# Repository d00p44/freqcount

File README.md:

# freqcount
accurate frequency counter

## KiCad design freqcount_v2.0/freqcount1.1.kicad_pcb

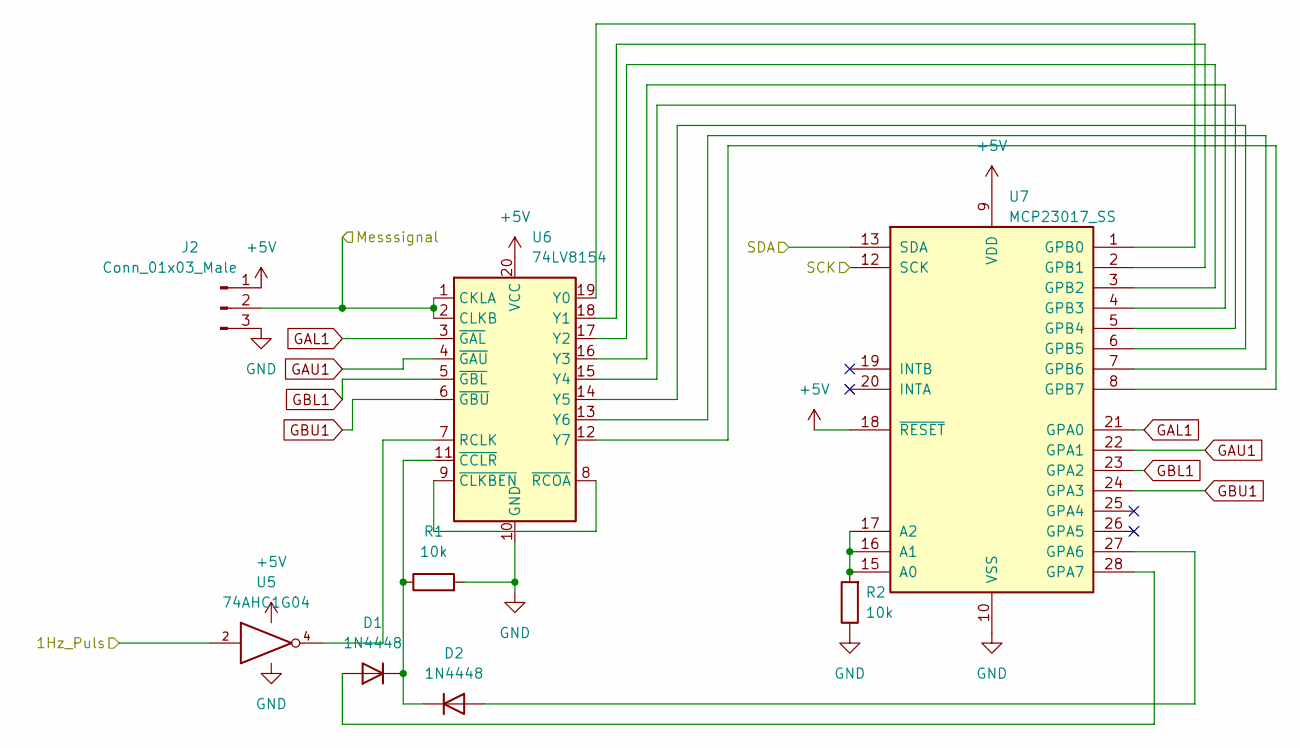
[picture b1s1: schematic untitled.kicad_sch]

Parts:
D1, D2: 1N4448; D_SOD-323
J2: Conn_01x03_Male; JST_PH_B3B-PH-K_1x03_P2.00mm_Vertical
R1, R2: 10k; R_0603_1608Metric
U5: 74AHC1G04; SOT-23-5
U6: 74LV8154; TSSOP-20_4.4x6.5mm_P0.65mm
U7: MCP23017_SS; SSOP-28_5.3x10.2mm_P0.65mm

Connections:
+5V: J2.1, U5.5 (VCC), U6.20 (VCC), U7.9 (VDD), U7.18 (~RESET); also elsewhere on the board
/ESP/SCK: U7.12 (SCK); also elsewhere on the board
/ESP/SDA: U7.13 (SDA); also elsewhere on the board
/Teiler_1Hz/1Hz_Puls: U5.2; also elsewhere on the board
/Zaehler_Messsignal/Messsignal: J2.2, U6.1 (CKLA), U6.2 (CLKB); also elsewhere on the board
GAL1: U6.3 (~GAL), U7.21 (GPA0)
GAU1: U6.4 (~GAU), U7.22 (GPA1)
GBL1: U6.5 (~GBL), U7.23 (GPA2)
GBU1: U6.6 (~GBU), U7.24 (GPA3)
GND: J2.3, R1.2, R2.1, U5.3 (GND), U6.10 (GND), U7.10 (VSS); also elsewhere on the board
unnamed: D1.1 (K), D2.1 (K), R1.1, U6.11 (~CCLR)
unnamed: D1.2 (A), U7.28 (GPA7)
unnamed: D2.2 (A), U7.27 (GPA6)
unnamed: R2.2, U7.15 (A0), U7.16 (A1), U7.17 (A2)
unnamed: U5.4, U6.7 (RCLK)
unnamed: U6.8 (~RCOA), U6.9 (~CLKBEN)
unnamed: U6.12 (Y7), U7.8 (GPB7)
unnamed: U6.13 (Y6), U7.7 (GPB6)
unnamed: U6.14 (Y5), U7.6 (GPB5)
unnamed: U6.15 (Y4), U7.5 (GPB4)
unnamed: U6.16 (Y3), U7.4 (GPB3)
unnamed: U6.17 (Y2), U7.3 (GPB2)
unnamed: U6.18 (Y1), U7.2 (GPB1)
unnamed: U6.19 (Y0), U7.1 (GPB0)

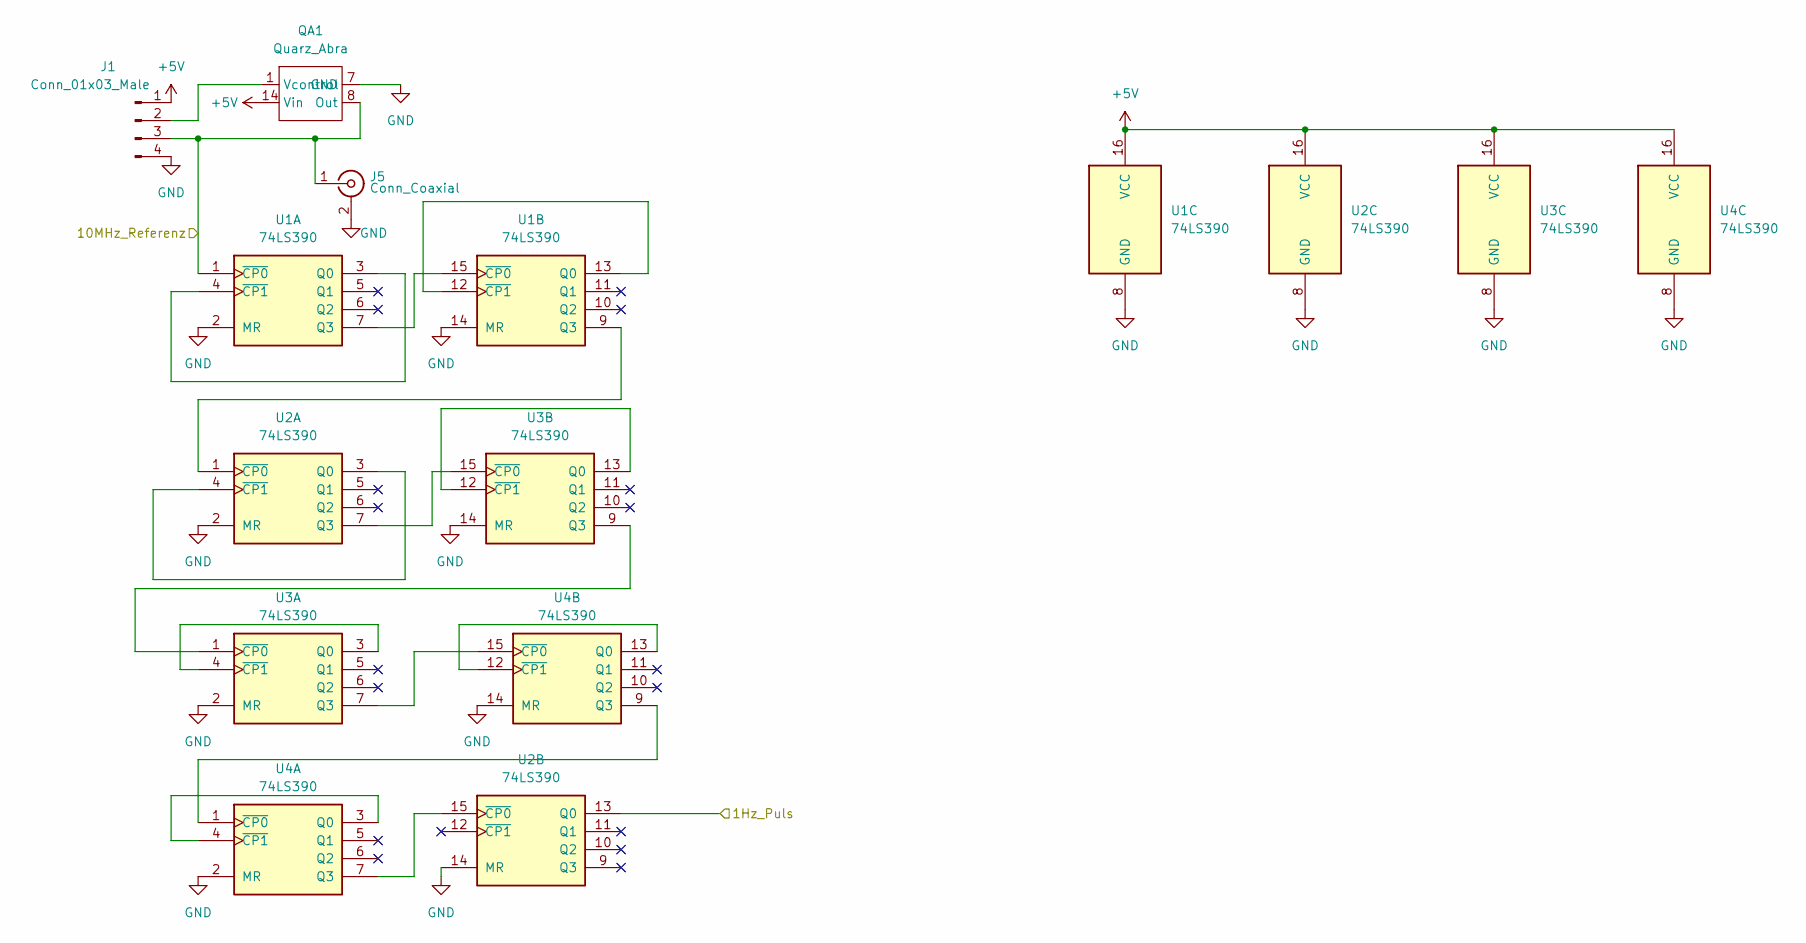
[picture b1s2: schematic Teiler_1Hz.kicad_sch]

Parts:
J1: Conn_01x03_Male; JST_PH_B4B-PH-K_1x04_P2.00mm_Vertical
J5: Conn_Coaxial; SMA_Amphenol_901-144_Vertical
QA1: Quarz_Abra; Quarz-Abra
U1, U2, U3, U4: 74LS390; SSOP-16_4.4x5.2mm_P0.65mm

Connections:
+5V: J1.1, QA1.14 (Vin), U1.16 (VCC), U2.16 (VCC), U3.16 (VCC), U4.16 (VCC); also elsewhere on the board
/Teiler_1Hz/1Hz_Puls: U2.13 (Q0); also elsewhere on the board
/Teiler_1Hz/10MHz_Referenz: J1.3, J5.1 (In), QA1.8 (Out), U1.1 (~CP0); also elsewhere on the board
GND: J1.4, J5.2 (Ext), QA1.7 (GND), U1.2 (MR), U1.8 (GND), U1.14 (MR), U2.2 (MR), U2.8 (GND), U2.14 (MR), U3.2 (MR), U3.8 (GND), U3.14 (MR), U4.2 (MR), U4.8 (GND), U4.14 (MR); also elsewhere on the board
unnamed: J1.2, QA1.1 (Vcontrol)
unnamed: U1.3 (Q0), U1.4 (~CP1)
unnamed: U1.9 (Q3), U2.1 (~CP0)
unnamed: U1.12 (~CP1), U1.13 (Q0)
unnamed: U1.7 (Q3), U1.15 (~CP0)
unnamed: U2.3 (Q0), U2.4 (~CP1)
unnamed: U2.7 (Q3), U3.15 (~CP0)
unnamed: U2.15 (~CP0), U4.7 (Q3)
unnamed: U3.1 (~CP0), U3.9 (Q3)
unnamed: U3.3 (Q0), U3.4 (~CP1)
unnamed: U3.7 (Q3), U4.15 (~CP0)
unnamed: U3.12 (~CP1), U3.13 (Q0)
unnamed: U4.1 (~CP0), U4.9 (Q3)
unnamed: U4.3 (Q0), U4.4 (~CP1)
unnamed: U4.12 (~CP1), U4.13 (Q0)

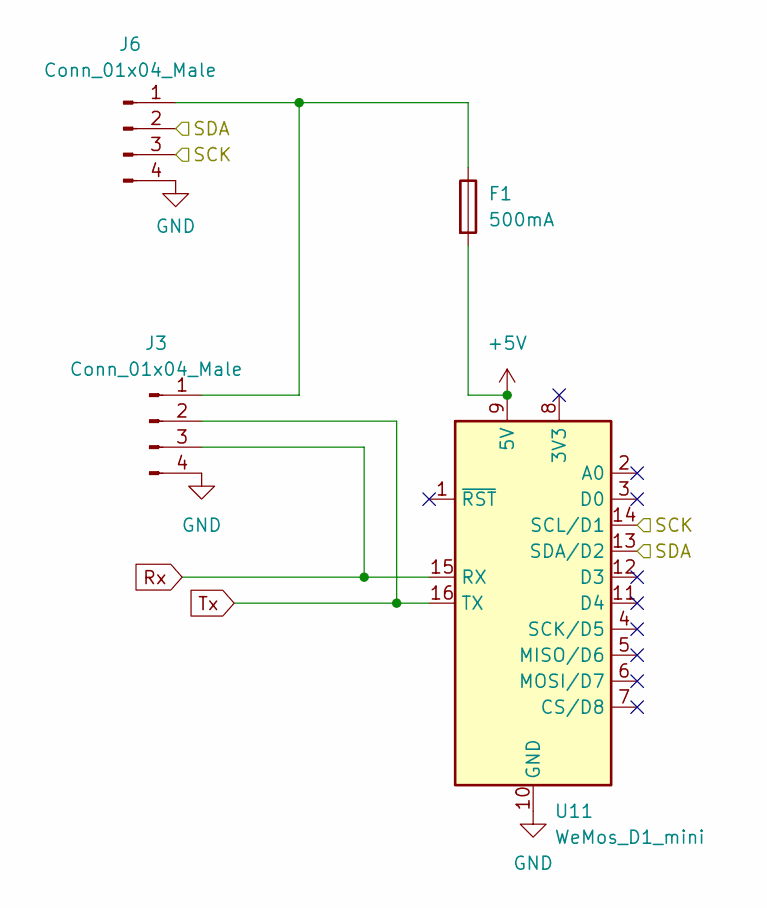
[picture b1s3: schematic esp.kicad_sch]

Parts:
F1: 500mA; Fuseholder_TR5_Littelfuse_No560_No460
J3, J6: Conn_01x04_Male; JST_PH_B4B-PH-K_1x04_P2.00mm_Vertical
U11: WeMos_D1_mini; WEMOS_D1_mini_light

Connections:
+5V: F1.2, U11.9 (5V); also elsewhere on the board
/ESP/SCK: J6.3, U11.14 (SCL/D1); also elsewhere on the board
/ESP/SDA: J6.2, U11.13 (SDA/D2); also elsewhere on the board
GND: J3.4, J6.4, U11.10 (GND); also elsewhere on the board
unnamed: F1.1, J3.1, J6.1
Rx: J3.3, U11.15 (RX)
Tx: J3.2, U11.16 (TX)

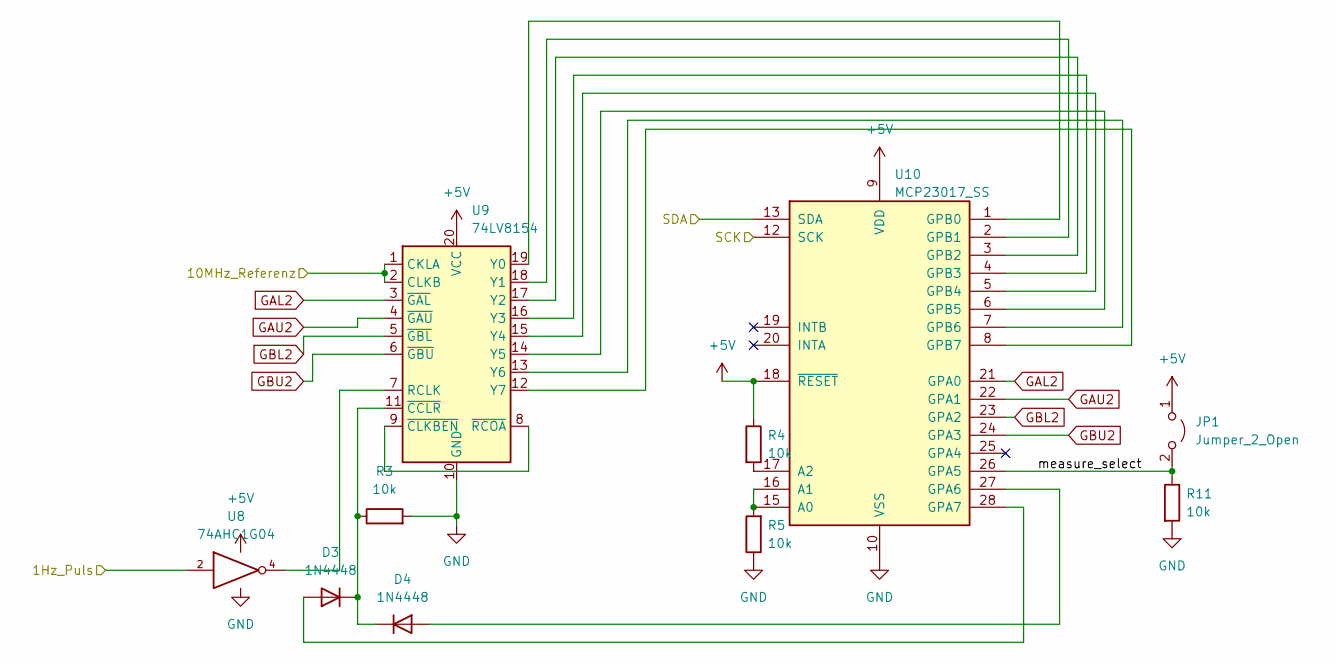
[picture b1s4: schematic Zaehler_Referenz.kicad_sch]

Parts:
D3, D4: 1N4448; D_SOD-323
JP1: Jumper_2_Open; PinHeader_1x02_P2.54mm_Vertical
R3, R4, R5, R11: 10k; R_0603_1608Metric
U8: 74AHC1G04; SOT-23-5
U9: 74LV8154; TSSOP-20_4.4x6.5mm_P0.65mm
U10: MCP23017_SS; SSOP-28_5.3x10.2mm_P0.65mm

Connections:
+5V: JP1.1 (A), R4.1, U8.5 (VCC), U9.20 (VCC), U10.9 (VDD), U10.18 (~RESET); also elsewhere on the board
/ESP/SCK: U10.12 (SCK); also elsewhere on the board
/ESP/SDA: U10.13 (SDA); also elsewhere on the board
/Teiler_1Hz/1Hz_Puls: U8.2; also elsewhere on the board
/Teiler_1Hz/10MHz_Referenz: U9.1 (CKLA), U9.2 (CLKB); also elsewhere on the board
/Zaehler_Referenz/measure_select: JP1.2 (B), R11.1, U10.26 (GPA5)
GAL2: U9.3 (~GAL), U10.21 (GPA0)
GAU2: U9.4 (~GAU), U10.22 (GPA1)
GBL2: U9.5 (~GBL), U10.23 (GPA2)
GBU2: U9.6 (~GBU), U10.24 (GPA3)
GND: R3.2, R5.1, R11.2, U8.3 (GND), U9.10 (GND), U10.10 (VSS); also elsewhere on the board
unnamed: D3.1 (K), D4.1 (K), R3.1, U9.11 (~CCLR)
unnamed: D3.2 (A), U10.28 (GPA7)
unnamed: D4.2 (A), U10.27 (GPA6)
unnamed: R4.2, U10.17 (A2)
unnamed: R5.2, U10.15 (A0), U10.16 (A1)
unnamed: U8.4, U9.7 (RCLK)
unnamed: U9.8 (~RCOA), U9.9 (~CLKBEN)
unnamed: U9.19 (Y0), U10.1 (GPB0)
unnamed: U9.18 (Y1), U10.2 (GPB1)
unnamed: U9.17 (Y2), U10.3 (GPB2)
unnamed: U9.16 (Y3), U10.4 (GPB3)
unnamed: U9.15 (Y4), U10.5 (GPB4)
unnamed: U9.14 (Y5), U10.6 (GPB5)
unnamed: U9.13 (Y6), U10.7 (GPB6)
unnamed: U9.12 (Y7), U10.8 (GPB7)

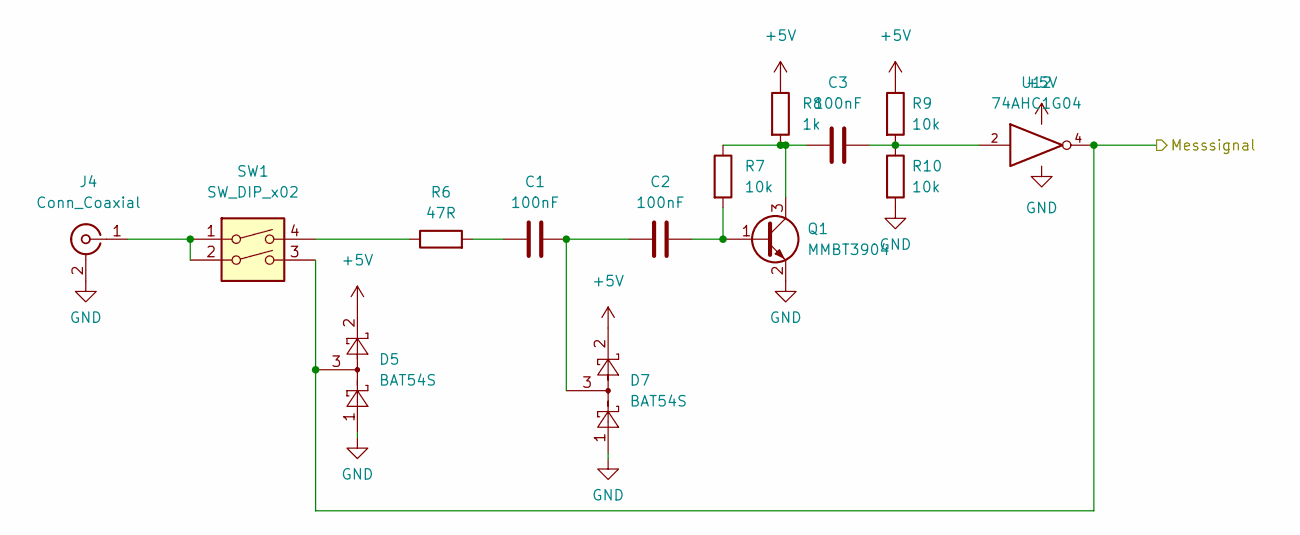
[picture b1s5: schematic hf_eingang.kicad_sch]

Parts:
C1, C2, C3: 100nF; C_0603_1608Metric
D5, D7: BAT54S; SOT-23
J4: Conn_Coaxial; SMA_Amphenol_901-144_Vertical
Q1: MMBT3904; SOT-23
R6: 47R; R_0603_1608Metric
R7, R9, R10: 10k; R_0603_1608Metric
R8: 1k; R_0603_1608Metric
SW1: SW_DIP_x02; DIP-4_W8.89mm_SMDSocket_LongPads
U12: 74AHC1G04; SOT-23-5

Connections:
+5V: D5.2, D7.2, R8.1, R9.1, U12.5 (VCC); also elsewhere on the board
/Zaehler_Messsignal/Messsignal: D5.3, SW1.3, U12.4; also elsewhere on the board
GND: D5.1, D7.1, J4.2 (Ext), Q1.2 (E), R10.2, U12.3 (GND); also elsewhere on the board
unnamed: C1.1, R6.2
unnamed: C1.2, C2.1, D7.3
unnamed: C2.2, Q1.1 (B), R7.2
unnamed: C3.1, Q1.3 (C), R7.1, R8.2
unnamed: C3.2, R9.2, R10.1, U12.2
unnamed: J4.1 (In), SW1.1, SW1.2
unnamed: R6.1, SW1.4

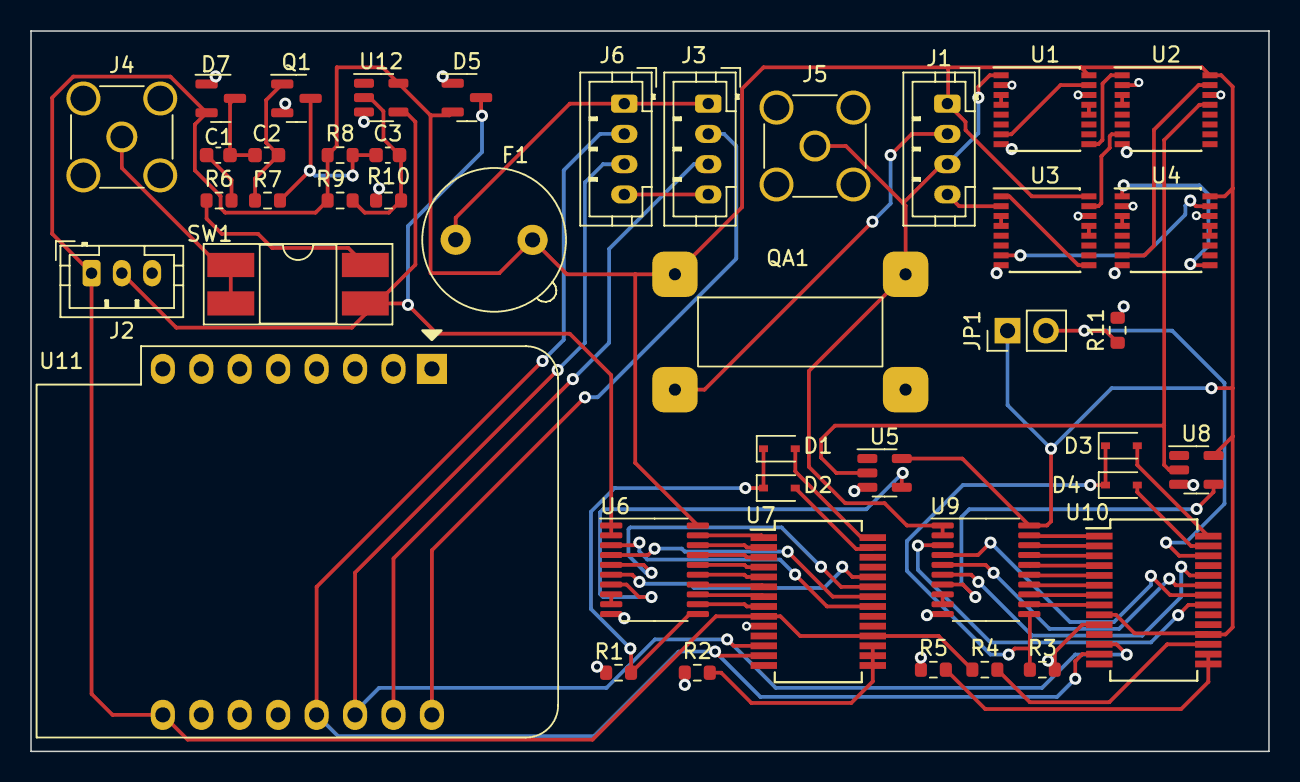
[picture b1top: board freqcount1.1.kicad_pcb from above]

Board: 2 copper layers, 81.8 x 47.6 mm, 43 parts (0 on the bottom side), 70 nets.

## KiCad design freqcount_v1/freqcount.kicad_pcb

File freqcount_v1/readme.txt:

-Cs am Quarz falsch angebunden 
-kein ISP-Stecker

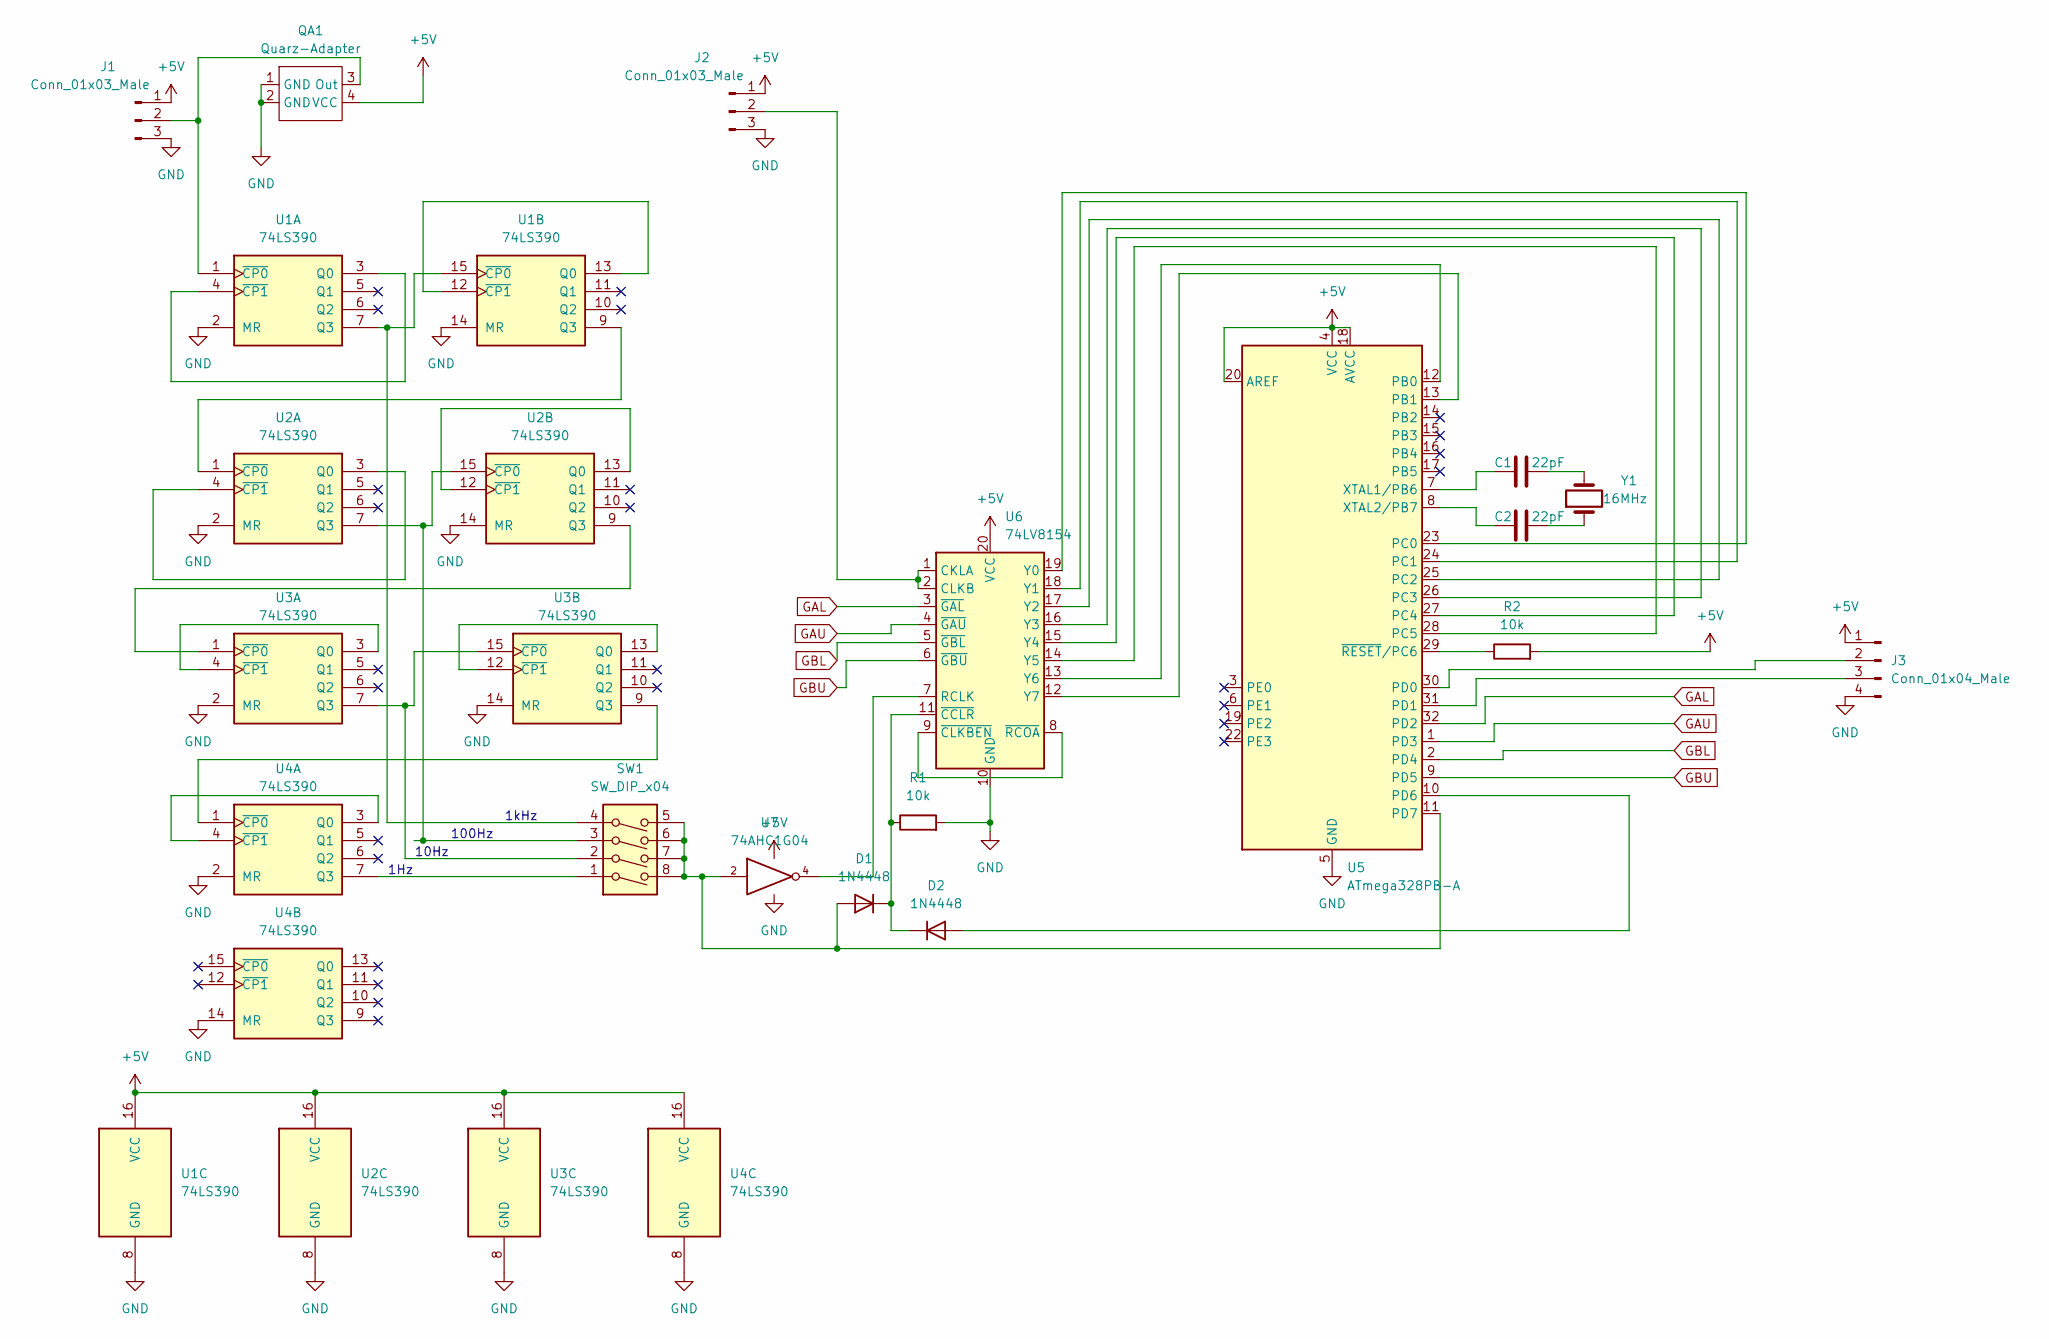
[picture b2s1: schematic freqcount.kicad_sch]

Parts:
C1, C2: 22pF; C_0603_1608Metric
D1, D2: 1N4448; D_SOD-323
J1, J2: Conn_01x03_Male; JST_PH_B3B-PH-K_1x03_P2.00mm_Vertical
J3: Conn_01x04_Male; JST_EH_B4B-EH-A_1x04_P2.50mm_Vertical
QA1: Quarz-Adapter
R1, R2: 10k; R_0603_1608Metric
SW1: SW_DIP_x04; SW_DIP_SPSTx04_Slide_KingTek_DSHP04TS_W7.62mm_P1.27mm
U1, U2, U3, U4: 74LS390; SSOP-16_4.4x5.2mm_P0.65mm
U5: ATmega328PB-A; TQFP-32_7x7mm_P0.8mm
U6: 74LV8154; TSSOP-20_4.4x6.5mm_P0.65mm
U7: 74AHC1G04; SOT-23-5
Y1: 16MHz; Crystal_SMD_EuroQuartz_MJ-4Pin_5.0x3.2mm

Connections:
+5V: J1.1, J2.1, J3.1, QA1.4 (VCC), R2.2, U1.16 (VCC), U2.16 (VCC), U3.16 (VCC), U4.16 (VCC), U5.4 (VCC), U5.18 (AVCC), U5.20 (AREF), U6.20 (VCC), U7.5 (VCC)
GAL: U5.32 (PD2), U6.3 (~GAL)
GAU: U5.1 (PD3), U6.4 (~GAU)
GBL: U5.2 (PD4), U6.5 (~GBL)
GBU: U5.9 (PD5), U6.6 (~GBU)
GND: J1.3, J2.3, J3.4, QA1.1 (GND), QA1.2 (GND), R1.2, U1.2 (MR), U1.8 (GND), U1.14 (MR), U2.2 (MR), U2.8 (GND), U2.14 (MR), U3.2 (MR), U3.8 (GND), U3.14 (MR), U4.2 (MR), U4.8 (GND), U4.14 (MR), U5.5 (GND), U5.21 (GND), U6.10 (GND), U7.3 (GND)
unnamed: C1.2, Y1.2
unnamed: C2.2, Y1.1
unnamed: D1.1 (K), D2.1 (K), R1.1, U6.11 (~CCLR)
unnamed: D2.2 (A), U5.10 (PD6)
unnamed: J1.2, QA1.3 (Out), U1.1 (~CP0)
unnamed: J2.2, U6.1 (CKLA), U6.2 (CLKB)
unnamed: R2.1, U5.29 (~RESET/PC6)
unnamed: SW1.3, U2.7 (Q3), U2.15 (~CP0)
unnamed: SW1.4, U1.7 (Q3), U1.15 (~CP0)
unnamed: U1.3 (Q0), U1.4 (~CP1)
unnamed: U1.12 (~CP1), U1.13 (Q0)
unnamed: U1.9 (Q3), U2.1 (~CP0)
unnamed: U2.3 (Q0), U2.4 (~CP1)
unnamed: U2.12 (~CP1), U2.13 (Q0)
unnamed: U2.9 (Q3), U3.1 (~CP0)
unnamed: U3.3 (Q0), U3.4 (~CP1)
unnamed: SW1.2, U3.7 (Q3), U3.15 (~CP0)
unnamed: U3.12 (~CP1), U3.13 (Q0)
unnamed: U3.9 (Q3), U4.1 (~CP0)
unnamed: U4.3 (Q0), U4.4 (~CP1)
unnamed: SW1.1, U4.7 (Q3)
unnamed: C1.1, U5.7 (XTAL1/PB6)
unnamed: C2.1, U5.8 (XTAL2/PB7)
unnamed: J3.2, U5.30 (PD0)
unnamed: J3.3, U5.31 (PD1)
unnamed: U6.7 (RCLK), U7.4
unnamed: U6.8 (~RCOA), U6.9 (~CLKBEN)
unnamed: U5.13 (PB1), U6.12 (Y7)
unnamed: U5.12 (PB0), U6.13 (Y6)
unnamed: U5.28 (PC5), U6.14 (Y5)
unnamed: U5.27 (PC4), U6.15 (Y4)
unnamed: U5.26 (PC3), U6.16 (Y3)
unnamed: U5.25 (PC2), U6.17 (Y2)
unnamed: U5.24 (PC1), U6.18 (Y1)
unnamed: U5.23 (PC0), U6.19 (Y0)
unnamed: D1.2 (A), SW1.5, SW1.6, SW1.7, SW1.8, U5.11 (PD7), U7.2

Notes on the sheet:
1kHz
100Hz
1Hz
10Hz

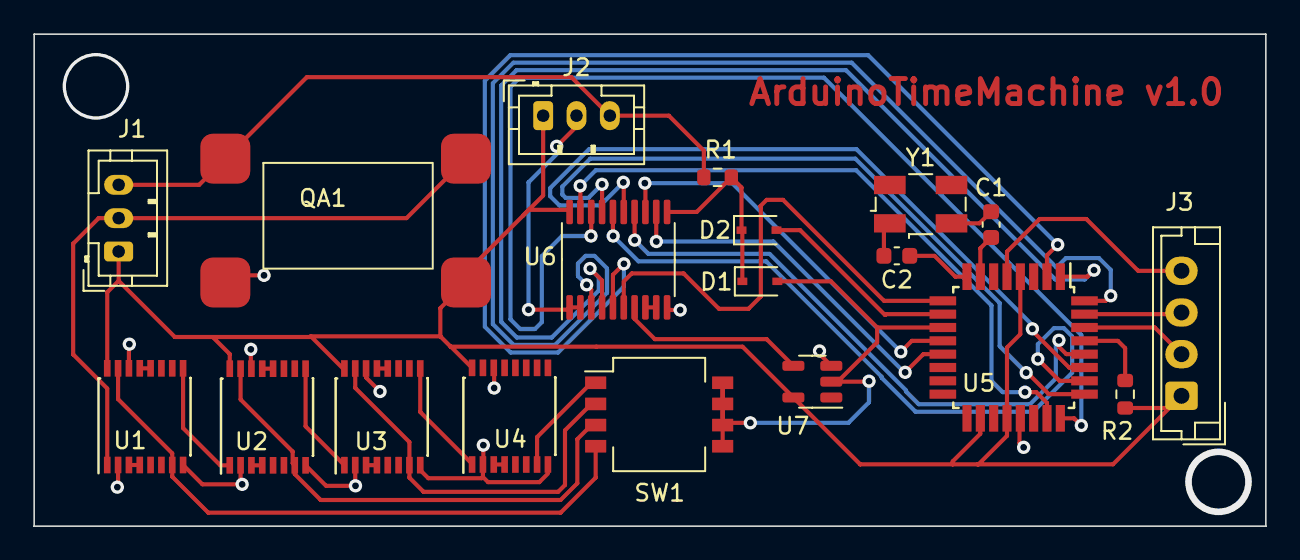
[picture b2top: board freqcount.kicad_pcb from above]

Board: 2 copper layers, 73.9 x 29.5 mm, 19 parts (0 on the bottom side), 42 nets.

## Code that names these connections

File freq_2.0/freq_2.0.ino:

#include <Wire.h>
#include <Arduino.h>
#include <Adafruit_MCP23017.h>
#include <ESP8266WiFi.h>  
// Define I/O pins

	#define GAL 0 // These pins select 1 of the 4 bytes of data to access
	#define GAU 1
	#define GBL 2
	#define GBU 3
	
	// Next 8 pins have the 8 bits of count data
	// Note I can read 0 thru 5 with PINC and 7 & 8 with PINB
	
	#define Y0 8 // A0 - A5 are PC0 - PC5
	#define Y1 9
	#define Y2 10
	#define Y3 11
	#define Y4 12
	#define Y5 13
	#define Y6 14
	#define Y7 15
	
	#define CE_Not 6 // V1.1x, pin formerly called latch, now enables clear
	#define C_state 7 // V1.1x, was 'clear' now monitors clock

  unsigned long freq;
  unsigned long ref;
  unsigned long rezi;

Adafruit_MCP23017 mcp2;
Adafruit_MCP23017 mcp3;

void setup(){
  Serial.begin(9600); //serial init
  WiFi.mode(WIFI_OFF); // to safe battery power

  mcp2.begin(0); // Init MCP23017 at address 0x20
  mcp3.begin(4);
  for (int i=8;i<=15;i++){  
     mcp2.pinMode(i, INPUT);
  }
  for (int i=0;i<=6;i++){  
     mcp2.pinMode(i, OUTPUT);
     mcp2.pullUp(i, HIGH);
     }
     mcp2.pinMode(C_state, INPUT);

//MCP3 init  

  for (int i=8;i<=15;i++){  
     mcp3.pinMode(i, INPUT);
  }
  for (int i=0;i<=6;i++){  
     mcp3.pinMode(i, OUTPUT);
     mcp3.pullUp(i, HIGH);
     }
     mcp3.pinMode(C_state, INPUT);  

  delay(500);
  Serial.println("Zaehler laeuft");
  while(!mcp2.digitalRead(C_state)){yield();} 
  while(mcp2.digitalRead(C_state)){yield();} 
  while(!mcp2.digitalRead(C_state)){yield();}
  //Clock is Running
  delay(500);
  Serial.println("Zaehler laeuft");
  
}


void loop(){ 

   count();
   delay(1);
    rezi= ref*freq;
    
    Serial.println(freq);  
    Serial.println(ref); 
    
    Serial.println(rezi); 

}

uint8_t get_byte()
	  {
		  uint8_t tempbyte;
		  
		  tempbyte = mcp2.readGPIO(1);
		  return tempbyte; // now we have the full 8 bits loaded
	  }
	
	// This routine will read all four bytes of frequency data and put
	// them in the long int 'freq'
uint8_t get_byte_ref()
	  {
		  uint8_t tempbyte_ref;
		  
		  tempbyte_ref = mcp3.readGPIO(1);
		  return tempbyte_ref; // now we have the full 8 bits loaded
	  }

	void read32()
	{

		mcp2.digitalWrite(GBU, LOW); // highest byte of four
		freq = (unsigned long) get_byte();
		freq = freq << 8;
		mcp2.digitalWrite(GBU, HIGH);
		
		mcp2.digitalWrite(GBL, LOW); // next highest
		freq = freq | (unsigned long) get_byte();
		freq = freq << 8;
		mcp2.digitalWrite(GBL, HIGH);
		
		mcp2.digitalWrite(GAU, LOW); // third - bits 8 - 15
		freq = freq | (unsigned long) get_byte();
		freq = freq << 8;
		mcp2.digitalWrite(GAU, HIGH);
		
		mcp2.digitalWrite(GAL, LOW); // lowest byte, b0:7
		freq = freq | (unsigned long) get_byte();
		mcp2.digitalWrite(GAL, HIGH);
		freq = freq*10;
		
	}
  void read32_ref()
	{

		mcp3.digitalWrite(GBU, LOW); // highest byte of four
		ref = (unsigned long) get_byte_ref();
		ref = ref << 8;
		mcp3.digitalWrite(GBU, HIGH);
		
		mcp3.digitalWrite(GBL, LOW); // next highest
		ref = ref | (unsigned long) get_byte_ref();
		ref = ref << 8;
		mcp3.digitalWrite(GBL, HIGH);
		
		mcp3.digitalWrite(GAU, LOW); // third - bits 8 - 15
		ref = ref | (unsigned long) get_byte_ref();
		ref = ref << 8;
		mcp3.digitalWrite(GAU, HIGH);
		
		mcp3.digitalWrite(GAL, LOW); // lowest byte, b0:7
		ref = ref | (unsigned long) get_byte_ref();
		mcp3.digitalWrite(GAL, HIGH);
		ref = ref*10;
		
	}
  void count(){
  while(mcp2.digitalRead(C_state)){yield();} // stay until LOW
	
	// Now a counting period has ended and data being latched
	delay(1); // allow 2 ms to latch before clear
	mcp2.digitalWrite(CE_Not, LOW); // allow low clock to reach -CCLR
  mcp3.digitalWrite(CE_Not, LOW);
	// Now, clock will determine when to remove clear signal
	
	read32();
  read32_ref();
  while(!mcp2.digitalRead(C_state)){yield();}// Stay until HIGH and loop back
	mcp2.digitalWrite(CE_Not, HIGH);
  mcp3.digitalWrite(CE_Not, HIGH);
  }

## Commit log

2023-07-26 Add files via upload
    modified version of espboy_firsttest to run freq count on espboy
2023-10-13 Firmware for v2
2025-06-13 Add files via upload
    firmware with reziprok counter
